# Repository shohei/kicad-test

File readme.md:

# kicad test
## rev1

## rev2 自動配線

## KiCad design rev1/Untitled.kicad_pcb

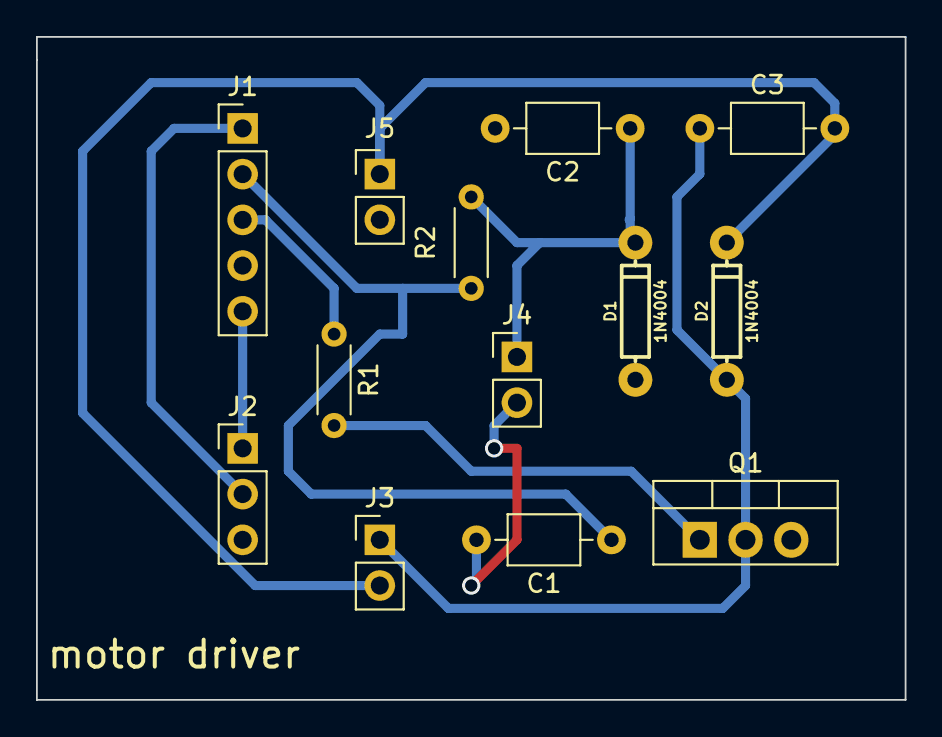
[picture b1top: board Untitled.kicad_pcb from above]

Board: 2 copper layers, 48.3 x 36.8 mm, 13 parts (0 on the bottom side), 9 nets.

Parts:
C1, C2, C3: 0.1u; C_Axial_L3.8mm_D2.6mm_P7.50mm_Horizontal
D1, D2: 1N4004; DIODE-1N4148
J1: ARDUINO; PinHeader_1x05_P2.54mm_Vertical
J2: POT; PinHeader_1x03_P2.54mm_Vertical
J3: MOTOR; PinHeader_1x02_P2.54mm_Vertical
J4: TACHO; PinHeader_1x02_P2.54mm_Vertical
J5: BAT; PinHeader_1x02_P2.54mm_Vertical
Q1: 2SK2341; TO-220-3_Vertical
R1: 1.5k; R_Axial_DIN0204_L3.6mm_D1.6mm_P5.08mm_Horizontal
R2: 100k; R_Axial_DIN0204_L3.6mm_D1.6mm_P5.08mm_Horizontal

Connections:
GND: C1.2, C2.2, D1.A, J1.4, J2.3, J4.2, J5.2, Q1.3 (S)
unnamed: C1.1, J1.2, R2.1
unnamed: C2.1, D1.C, J4.1, R2.2
unnamed: C3.1, D2.A, J3.1, Q1.2 (D)
unnamed: C3.2, D2.C, J3.2, J5.1
unnamed: J1.1, J2.2
unnamed: J1.3, R1.1
unnamed: Q1.1 (G), R1.2
VCC: J1.5, J2.1

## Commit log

2022-05-15 add images
